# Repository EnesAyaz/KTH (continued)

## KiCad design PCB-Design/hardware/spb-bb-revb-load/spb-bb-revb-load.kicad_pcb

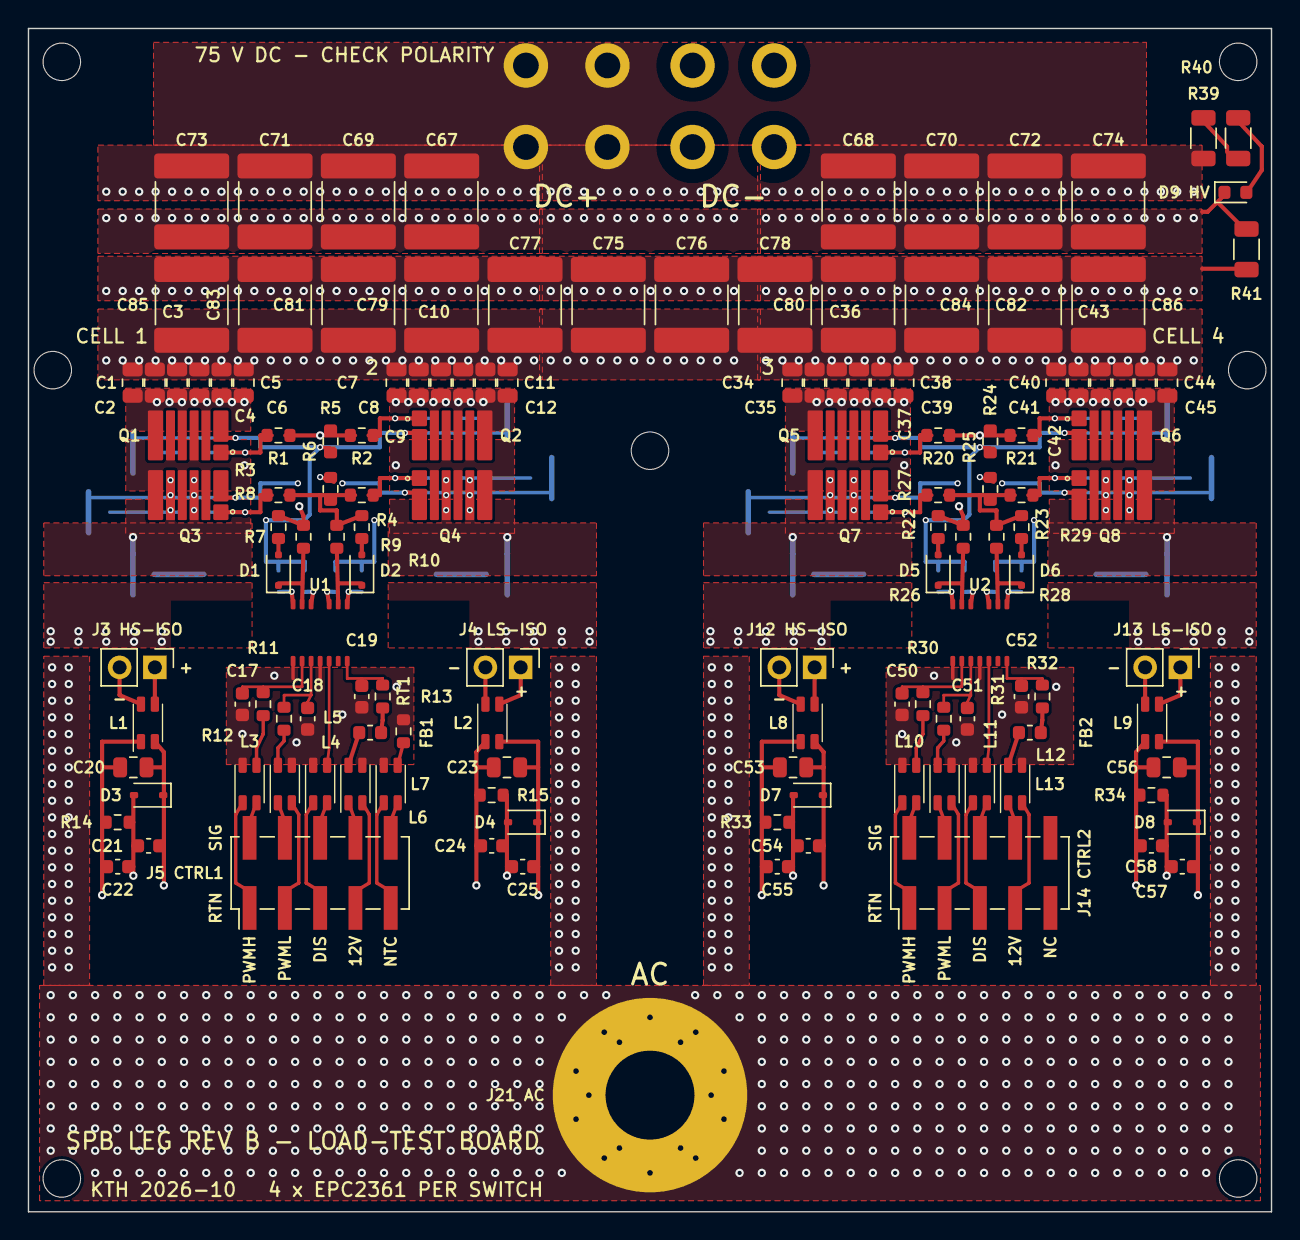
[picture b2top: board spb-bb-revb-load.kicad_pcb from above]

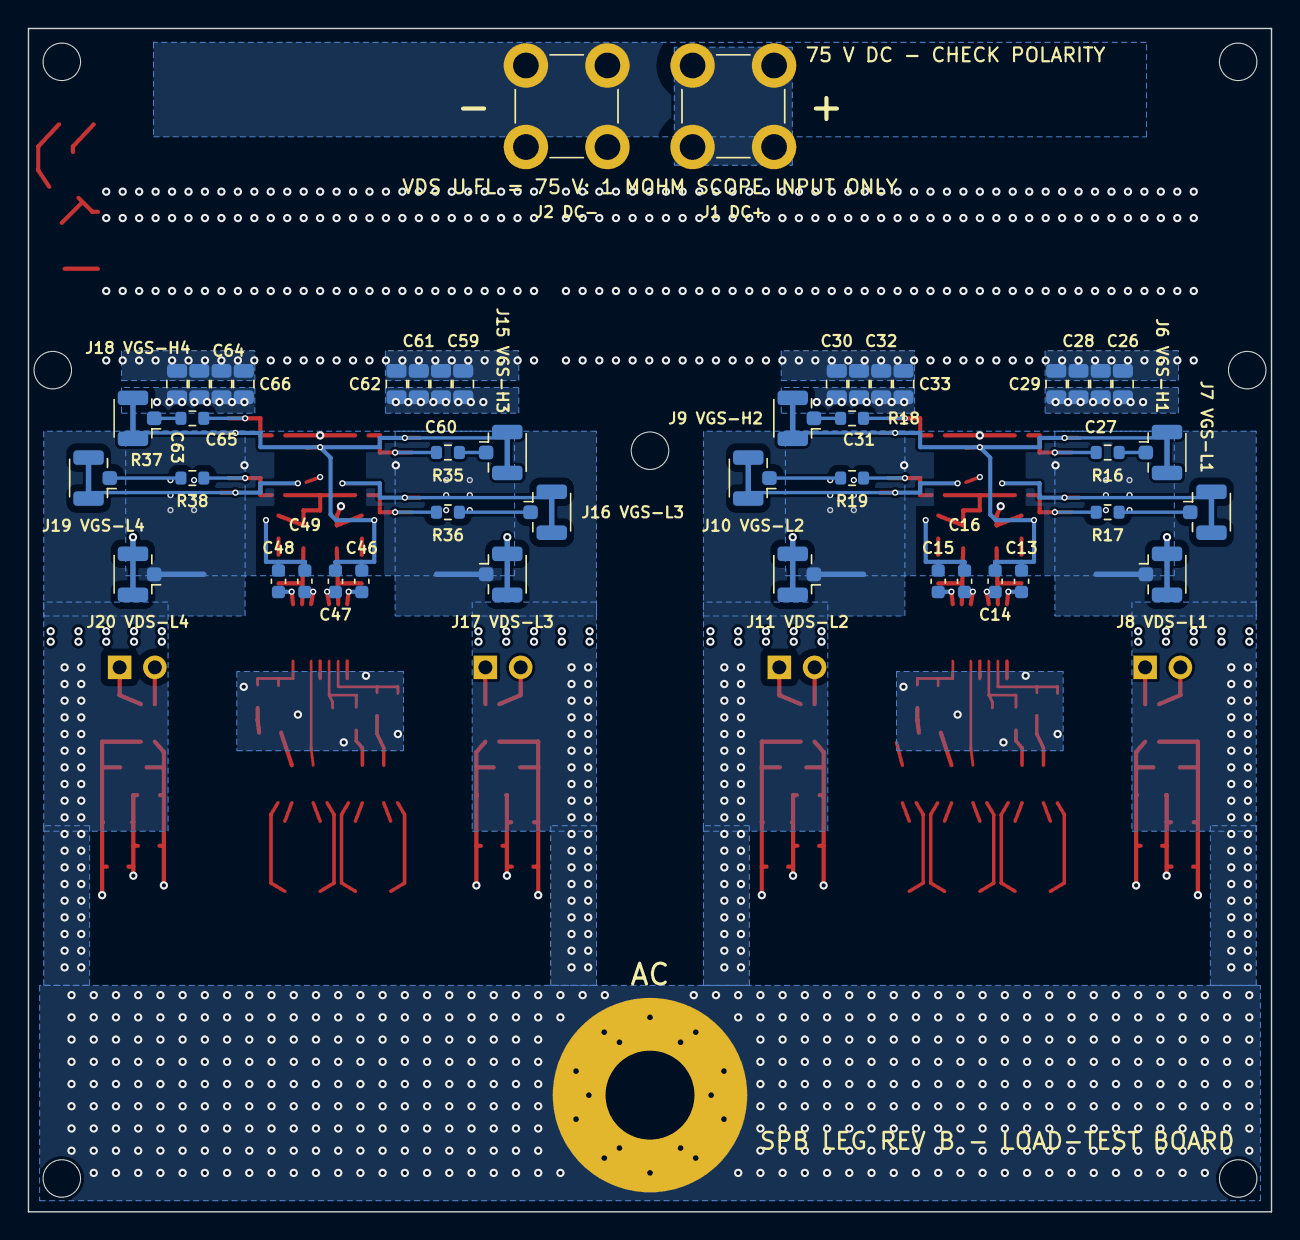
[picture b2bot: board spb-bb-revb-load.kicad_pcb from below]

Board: 4 copper layers, 89.5 x 85.2 mm, 191 parts (46 on the bottom side), 90 nets.

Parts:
C1, C2, C3, C4, C5, C6, C7, C8, C9, C10, C11, C12, C26, C27, C28, C29, C30, C31, C32, C33, C34, C35, C36, C37, C38, C39, C40, C41, C42, C43, C44, C45, C59, C60, C61, C62, C63, C64, C65, C66: 1uF 100V X7S; C_0805_2012Metric_TightCrtYd
C13, C14, C15, C16, C46, C47, C48, C49: 1uF 25V X7R 0603; C_0603_1608Metric
C17, C18, C50, C51: 100pF C0G 0603; C_0603_1608Metric
C19, C52: 22nF 25V X7R 0603; C_0603_1608Metric
C20, C23, C53, C56: 4.7uF 25V X7R 0805; C_0805_2012Metric
C21, C22, C24, C25, C54, C55, C57, C58: 4.7uF 16V X5R 0603; C_0603_1608Metric
C67, C68, C69, C70, C71, C72, C73, C74, C75, C76, C77, C78, C79, C80, C81, C82, C83, C84, C85, C86: 22uF 100V X7S 2220; C_2220_5750Metric_TightCrtYd
D1, D2, D5, D6: PMEG3020EJ; D_SOD-323F
D3, D4, D7, D8: BZX384-C5V1; D_SOD-323
D9: red 0603 (DC link present); LED_0603_1608Metric
FB1, FB2: BLM18PG221SN1 (220 R @ 100 MHz); L_0603_1608Metric
H1, H2, H3, H4: M2.5 insulated; MountingHole_2.7mm_M2.5
H5, H6, H7: M2.5 heatsink spreader; MountingHole_2.7mm_M2.5
HS1: Fischer LAM 4 K 50 12 + spreader; HS_LAM4K5012_revb
J1: DC+; Wuerth_REDCUBE-THR_WP-THRBU_74650174_THR
J2: DC-; Wuerth_REDCUBE-THR_WP-THRBU_74650174_THR
J3, J12: V_ISO,HS in: 1 +, 2 -; PinHeader_1x02_P2.54mm_Vertical
J4, J13: V_ISO,LS in: 1 +, 2 -; PinHeader_1x02_P2.54mm_Vertical
J5: CTRL1: 1 RTN 2 PWMH 3 RTN 4 PWML 5 RTN 6 DIS 7 RT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; PinHeader_2x05_P2.54mm_Vertical_SMD
J6: U.FL H1; U.FL_Hirose_U.FL-R-SMT-1_Vertical
J7: U.FL L1; U.FL_Hirose_U.FL-R-SMT-1_Vertical
J8: U.FL D1; U.FL_Hirose_U.FL-R-SMT-1_Vertical
J9: U.FL H2; U.FL_Hirose_U.FL-R-SMT-1_Vertical
J10: U.FL L2; U.FL_Hirose_U.FL-R-SMT-1_Vertical
J11: U.FL D2; U.FL_Hirose_U.FL-R-SMT-1_Vertical
J14: CTRL2: 1 RTN 2 PWMH 3 RTN 4 PWML 5 RTN 6 DIS 7 RT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; PinHeader_2x05_P2.54mm_Vertical_SMD
J15: U.FL H3; U.FL_Hirose_U.FL-R-SMT-1_Vertical
J16: U.FL L3; U.FL_Hirose_U.FL-R-SMT-1_Vertical
J17: U.FL D3; U.FL_Hirose_U.FL-R-SMT-1_Vertical
J18: U.FL H4; U.FL_Hirose_U.FL-R-SMT-1_Vertical
J19: U.FL L4; U.FL_Hirose_U.FL-R-SMT-1_Vertical
J20: U.FL D4; U.FL_Hirose_U.FL-R-SMT-1_Vertical
J21: AC; AC_BOLT_M6
L1, L2, L3, L4, L5, L6, L7, L8, L9, L10, L11, L12, L13: WE-CNSW 744232601; L_CommonMode_Wurth_WE-CNSW-1206
Q1, Q2, Q3, Q4, Q5, Q6, Q7, Q8: EPC2361
R1, R20: 0R5 1% (R_G HL); R_0603_1608Metric
R2, R21: 0R5 1% (R_G HR); R_0603_1608Metric
R3, R22: 0R5 1% (R_G LL); R_0603_1608Metric
R4, R23: 0R5 1% (R_G LR); R_0603_1608Metric
R5, R24: 10k 1% (HS gate pull-down); R_0603_1608Metric
R6, R25: 10k 1% (LS gate pull-down); R_0603_1608Metric
R7, R26: 0R75 1% (R_ON,A); R_0603_1608Metric
R8, R27: 0R (R_OFF,A); R_0603_1608Metric
R9, R28: 0R75 1% (R_ON,B); R_0603_1608Metric
R10, R29: 0R (R_OFF,B); R_0603_1608Metric
R11, R30: 47R 1% (INA); R_0603_1608Metric
R12, R31: 47R 1% (INB); R_0603_1608Metric
R13, R32: 3k 1% (RVDDI); R_0603_1608Metric
R14, R15, R33, R34: 150R 1% 0603 (bias, <= 82 mW); R_0603_1608Metric
R16, R18, R35, R37: 0R (V_GS HS); R_0603_1608Metric
R17, R19, R36, R38: 0R (V_GS LS); R_0603_1608Metric
R39, R40: 68k 1206 (HV LED); R_1206_3216Metric
R41: 100k 1206 (bleeder); R_1206_3216Metric
RT1: NTC 10k B3380 0603; R_0603_1608Metric
U1, U2: 2EDF7275K; 2EDF7275K_PG-TFLGA-13-4

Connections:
12V_CM1: FB1.1, L6.2
12V_CM2: FB2.1, L13.2
+12V1: FB1.2, R13.1
+12V2: FB2.2, R32.1
C_12V1: J5.8, L6.1
C_12V2: J14.8, L13.1
C_DIS1: J5.6, L5.4
C_DIS2: J14.6, L12.4
C_NTC1: J5.10, L7.4
C_PWMH1: J5.2, L3.4
C_PWMH2: J14.2, L10.4
C_PWML1: J5.4, L4.1
C_PWML2: J14.4, L11.1
C_RTN_12V1: J5.7, L6.4
C_RTN_12V2: J14.7, L13.4
C_RTN_DIS1: J5.5, L5.1
C_RTN_DIS2: J14.5, L12.1
C_RTN_NTC1: J5.9, L7.1
C_RTN_PWMH1: J5.1, L3.1
C_RTN_PWMH2: J14.1, L10.1
C_RTN_PWML1: J5.3, L4.4
C_RTN_PWML2: J14.3, L11.4
DCN: C1.2, C2.2, C3.2, C4.2, C5.2, C6.2, C7.2, C8.2, C9.2, C10.2, C11.2, C12.2, C26.1, C27.1, C28.1, C29.1, C30.1, C31.1, C32.1, C33.1, C34.2, C35.2, C36.2, C37.2, C38.2, C39.2, C40.2, C41.2, C42.2, C43.2, C44.2, C45.2, C59.1, C60.1, C61.1, C62.1, C63.1, C64.1, C65.1, C66.1, C67.1, C68.1, C69.1, C70.1, C71.1, C72.1, C73.1, C74.1, C75.1, C76.1, C77.1, C78.1, C79.1, C80.1, C81.1, C82.1, C83.1, C84.1, C85.1, C86.1, D9.1, J2.1, J8.2, J11.2, J17.2, J20.2, Q3.4, Q3.6, Q4.4, Q4.6, Q7.4, Q7.6, Q8.4, Q8.6, R41.2
DCP: C1.1, C2.1, C3.1, C4.1, C5.1, C6.1, C7.1, C8.1, C9.1, C10.1, C11.1, C12.1, C26.2, C27.2, C28.2, C29.2, C30.2, C31.2, C32.2, C33.2, C34.1, C35.1, C36.1, C37.1, C38.1, C39.1, C40.1, C41.1, C42.1, C43.1, C44.1, C45.1, C59.2, C60.2, C61.2, C62.2, C63.2, C64.2, C65.2, C66.2, C67.2, C68.2, C69.2, C70.2, C71.2, C72.2, C73.2, C74.2, C75.2, C76.2, C77.2, C78.2, C79.2, C80.2, C81.2, C82.2, C83.2, C84.2, C85.2, C86.2, J1.1, Q1.3, Q1.5, Q1.7, Q2.3, Q2.5, Q2.7, Q5.3, Q5.5, Q5.7, Q6.3, Q6.5, Q6.7, R39.1, R41.1
DIS1: L5.3, U1.5
DIS2: L12.3, U2.5
GH_L1: Q1.1, R1.1, R16.2
GH_L2: Q5.1, R20.1, R35.2
GH_R1: Q2.1, R2.2, R18.1
GH_R2: Q6.1, R21.2, R37.1
GH_STAR1: R1.2, R2.1, R5.2, R7.2, R8.2
GH_STAR2: R20.2, R21.1, R24.2, R26.2, R27.2
GL_L1: Q3.1, R3.1, R17.2
GL_L2: Q7.1, R22.1, R36.2
GL_R1: Q4.1, R4.2, R19.1
GL_R2: Q8.1, R23.2, R38.1
GL_STAR1: R3.2, R4.1, R6.1, R9.2, R10.2
GL_STAR2: R22.2, R23.1, R25.1, R28.2, R29.2
GNDI1: C17.1, C18.1, C19.1, L3.2, L4.3, L5.2, L6.3, L7.2, RT1.2, U1.1, U1.4
GNDI2: C50.1, C51.1, C52.1, L10.2, L11.3, L12.2, L13.3, U2.1, U2.4
HVA: R39.2, R40.1
HVB: D9.2, R40.2
INA1: C17.2, R11.2, U1.2
INA2: C50.2, R30.2, U2.2
INB1: C18.2, R12.2, U1.3
INB2: C51.2, R31.2, U2.3
KH1: C13.1, C14.1, C21.1, C22.2, D3.2, J6.2, J9.2, Q1.2, Q2.2, R5.1, R14.2
KH2: C46.1, C47.1, C54.1, C55.2, D7.2, J15.2, J18.2, Q5.2, Q6.2, R24.1, R33.2
KL1: C15.1, C16.1, C24.2, C25.1, D4.2, J7.2, J10.2, Q3.2, Q4.2, R6.2, R15.2
KL2: C48.1, C49.1, C57.2, C58.1, D8.2, J16.2, J19.2, Q7.2, Q8.2, R25.2, R34.2
NTC: L7.3, RT1.1
OFFA1: D1.2, R8.1
OFFA2: D5.2, R27.1
OFFB1: D2.2, R10.1
OFFB2: D6.2, R29.1
OUTA1: D1.1, R7.1, U1.12
OUTA2: D5.1, R26.1, U2.12
OUTB1: D2.1, R9.1, U1.9
OUTB2: D6.1, R28.1, U2.9
PWM_H1: L3.3, R11.1
PWM_H2: L10.3, R30.1
PWM_L1: L4.2, R12.1
PWM_L2: L11.2, R31.1
SW: J8.1, J11.1, J17.1, J20.1, J21.1, Q1.4, Q1.6, Q2.4, Q2.6, Q3.3, Q3.5, Q3.7, Q4.3, Q4.5, Q4.7, Q5.4, Q5.6, Q6.4, Q6.6, Q7.3, Q7.5, Q7.7, Q8.3, Q8.5, Q8.7
UFL_H1: J6.1, R16.1
UFL_H2: J9.1, R18.2
UFL_H3: J15.1, R35.1
UFL_H4: J18.1, R37.2
UFL_L1: J7.1, R17.1
UFL_L2: J10.1, R19.2
UFL_L3: J16.1, R36.1
UFL_L4: J19.1, R38.2
VDDA1: C13.2, C20.2, C21.2, D3.1, L1.4, U1.13
VDDA2: C46.2, C53.2, C54.2, D7.1, L8.4, U2.13
VDDB1: C16.2, C23.2, C25.2, D4.1, L2.4, U1.10
VDDB2: C49.2, C56.2, C58.2, D8.1, L9.4, U2.10
VDDI1: C19.2, R13.2, U1.7
VDDI2: C52.2, R32.2, U2.7
VEEA1: C14.2, C20.1, C22.1, L1.1, R14.1, U1.11
VEEA2: C47.2, C53.1, C55.1, L8.1, R33.1, U2.11
VEEB1: C15.2, C23.1, C24.1, L2.1, R15.1, U1.8
VEEB2: C48.2, C56.1, C57.1, L9.1, R34.1, U2.8
VINA_N1: J3.2, L1.2
VINA_N2: J12.2, L8.2
VINA_P1: J3.1, L1.3
VINA_P2: J12.1, L8.3
VINB_N1: J4.2, L2.2
VINB_N2: J13.2, L9.2
VINB_P1: J4.1, L2.3
VINB_P2: J13.1, L9.3

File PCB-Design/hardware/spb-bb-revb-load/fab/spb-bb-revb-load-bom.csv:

"# 4 layers, 1.6 mm FR4, 2 oz (70 um) on all layers, L1-L2 and L3-L4 prepreg 0.1 mm, ENIG; BLIND vias L1-L2 (0.25 mm drill) filled + capped in the LS source pads; load-test board; IPC class 2; solder mask over all copper and ALL vias tented (the 1200 V control/power barrier relies on it)"
Qty,References,Value,Footprint,Manufacturer part / note,Fit
2,J1 J2,DC+,Wuerth_REDCUBE-THR_WP-THRBU_74650174_THR,"Wuerth 74650174 (REDCUBE THR, M4)",fit
8,Q1 Q2 Q3 Q4 Q5 Q6 Q7 Q8,EPC2361,EPC2361,EPC2361,fit
40,C1 C10 C11 C12 C2 C26 C27 C28 C29 C3 C30 C31 C32 C33 C34 C35 C36 C37 C38 C39 C4 C40 C41 C42 C43 C44 C45 C5 C59 C6 C60 C61 C62 C63 C64 C65 C66 C7 C8 C9,1uF 100V X7S,C_0805_2012Metric_TightCrtYd,TDK C2012X7S2A105K125AB,fit
8,R1 R2 R20 R21 R22 R23 R3 R4,0R5 1% (R_G HL),R_0603_1608Metric,0.5R 0603 1% (Panasonic ERJ-3BQFR50V),fit
4,R24 R25 R5 R6,10k 1% (HS gate pull-down),R_0603_1608Metric,10k 0603 1%,fit
2,U1 U2,2EDF7275K,2EDF7275K_PG-TFLGA-13-4,Infineon 2EDF7275KXUMA1,fit
4,R26 R28 R7 R9,"0R75 1% (R_ON,A)",R_0603_1608Metric,0.75R 0603 1% (Panasonic ERJ-3RQFR75V),fit
4,R10 R27 R29 R8,"0R (R_OFF,A)",R_0603_1608Metric,0R 0603 jumper (set R_OFF here),fit
4,D1 D2 D5 D6,PMEG3020EJ,D_SOD-323F,"Nexperia PMEG3020EJ (30 V, 2 A, SOD323F)",fit
8,C13 C14 C15 C16 C46 C47 C48 C49,1uF 25V X7R 0603,C_0603_1608Metric,TDK C1608X7R1E105K080AB,fit
4,C17 C18 C50 C51,100pF C0G 0603,C_0603_1608Metric,Murata GRM1885C1H101JA01,fit
4,R11 R12 R30 R31,47R 1% (INA),R_0603_1608Metric,47R 0603 1%,fit
2,C19 C52,22nF 25V X7R 0603,C_0603_1608Metric,Murata GRM188R71E223KA01,fit
2,R13 R32,3k 1% (RVDDI),R_0603_1608Metric,3.0k 0603 1%,fit
4,J12 J13 J3 J4,"V_ISO,HS in: 1 +, 2 -",PinHeader_1x02_P2.54mm_Vertical,2.54 mm header 1x2,fit
13,L1 L10 L11 L12 L13 L2 L3 L4 L5 L6 L7 L8 L9,WE-CNSW 744232601,L_CommonMode_Wurth_WE-CNSW-1206,"Wurth 744232601 (600 Ohm @ 100 MHz, 260 mA)",fit
4,C20 C23 C53 C56,4.7uF 25V X7R 0805,C_0805_2012Metric,Murata GRM21BR71E475KA73,fit
4,D3 D4 D7 D8,BZX384-C5V1,D_SOD-323,"Nexperia BZX384-C5V1 (5.1 V, 300 mW)",fit
4,R14 R15 R33 R34,"150R 1% 0603 (bias, <= 82 mW)",R_0603_1608Metric,150R 0603 1% 0.1 W,fit
8,C21 C22 C24 C25 C54 C55 C57 C58,4.7uF 16V X5R 0603,C_0603_1608Metric,Murata GRM188R61C475KAAJ,fit
2,J14 J5,CTRL1: 1 RTN 2 PWMH 3 RTN 4 PWML 5 RTN 6 DIS 7 RTN 8 12V 9 RTN 10 NTC,PinHeader_2x05_P2.54mm_Vertical_SMD,"Samtec TSM-105-01-T-DV (2 x 5, 2.54 mm, SMT)",fit
2,FB1 FB2,BLM18PG221SN1 (220 R @ 100 MHz),L_0603_1608Metric,"Murata BLM18PG221SN1D (ferrite bead, 1.4 A)",fit
1,RT1,NTC 10k B3380 0603,R_0603_1608Metric,Murata NCP18XH103F03RB,fit
8,J10 J15 J16 J18 J19 J6 J7 J9,U.FL H1,U.FL_Hirose_U.FL-R-SMT-1_Vertical,Hirose U.FL-R-SMT-1(10),fit
8,R16 R17 R18 R19 R35 R36 R37 R38,0R (V_GS HS),R_0603_1608Metric,0R 0603,fit
4,J11 J17 J20 J8,U.FL D1,U.FL_Hirose_U.FL-R-SMT-1_Vertical,"Hirose U.FL-R-SMT-1(01) - 100 V listed, confirm",fit
20,C67 C68 C69 C70 C71 C72 C73 C74 C75 C76 C77 C78 C79 C80 C81 C82 C83 C84 C85 C86,22uF 100V X7S 2220,C_2220_5750Metric_TightCrtYd,TDK C5750X7S2A226M280KB,fit
2,R39 R40,68k 1206 (HV LED),R_1206_3216Metric,68k 1206 1% 200 V,fit
1,D9,red 0603 (DC link present),LED_0603_1608Metric,Wurth 150060RS75000,fit
1,R41,100k 1206 (bleeder),R_1206_3216Metric,100k 1206 1% 200 V,fit

Mechanical (not placed by the assembler)
1,HS1,"Fan heatsink 40 x 40 x 50 mm, 12 V fan",-,"Fischer Elektronik LAM 4 K 50 12 (0.65 K/W), Farnell 4708974"
1,HS1,Fan supply: 12 V from the bench supply (no fan header on the board: 1200 V barrier),-,-
2,"J5, J14",Control cable: 2 x 5 IDC socket + ribbon (each signal next to its own return),-,"2.54 mm IDC, e.g. Wurth 61201021621"
1,HS1,"Heat spreader Al 6061, 89.5 x 12.8 x 3 mm, 4 pedestals 5.6 x 7.7 x 0.6 mm over the cells, 3 x M2.5 (H5-H7)",-,machined
4,HS1,"Insulating gap pad over each cell, 5.6 x 7.7 mm, 0.5 mm, >= 5 W/mK",-,"Bergquist TGP 5000 0.020 in, cut to size, or equivalent"
3,H5-H7,M2.5 x 10 screw + insulating shoulder washer (spreader),-,nylon or steel + washer
4,H1-H4,M2.5 standoff + screw (H3/H4: nylon M2.5 x 6.5 mm onto the busbar),-,nylon
2,J1-J2,M4 x 8 screw + washer from below through the busbar into the REDCUBE,-,"steel, A2"
1,J22,"M6 x 16 bolt + nut + 2 washers, AC bolt pad",-,"steel, A2"
1,J22,AC bar 12 x 5 mm Cu through a LEM HO 250-S,-,Cu-ETP + LEM HO 250-S

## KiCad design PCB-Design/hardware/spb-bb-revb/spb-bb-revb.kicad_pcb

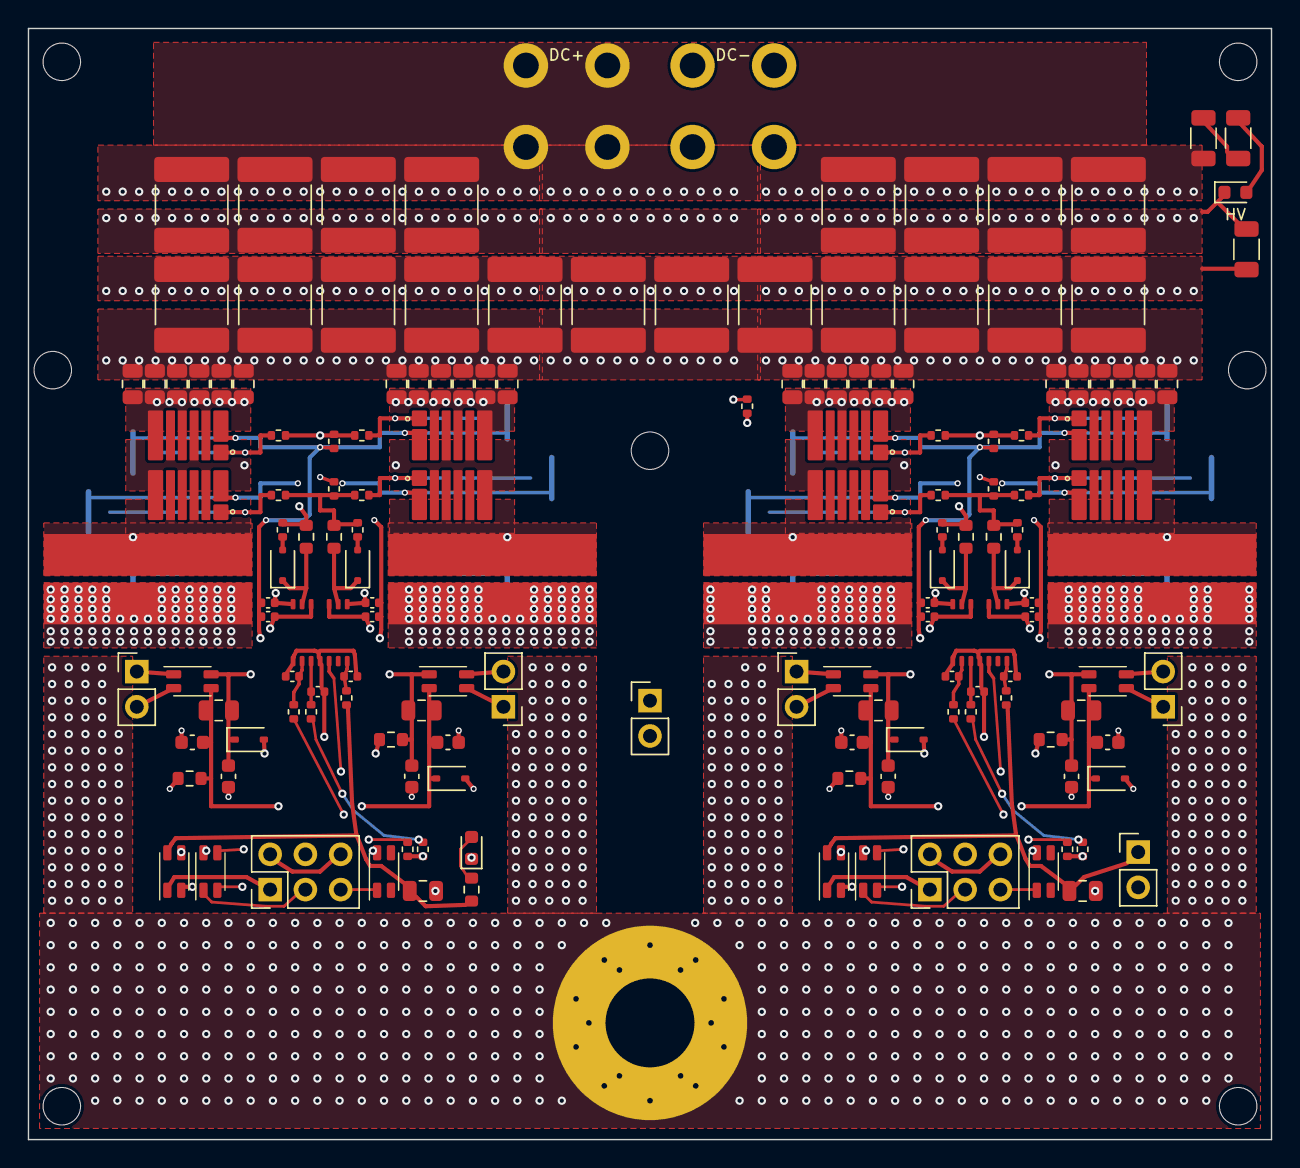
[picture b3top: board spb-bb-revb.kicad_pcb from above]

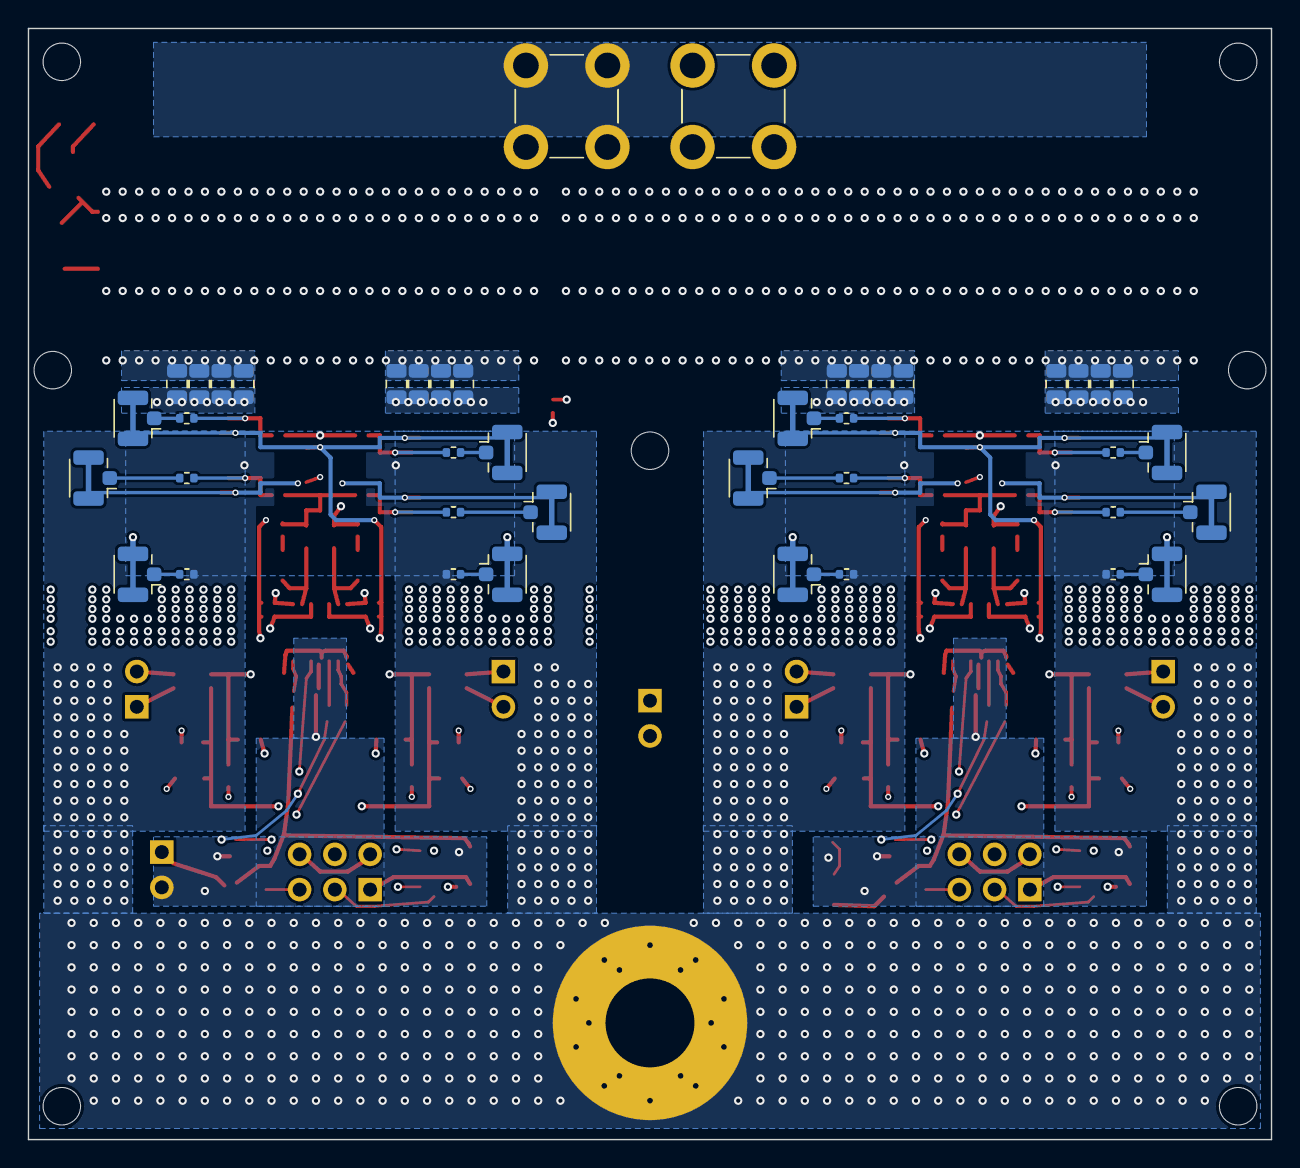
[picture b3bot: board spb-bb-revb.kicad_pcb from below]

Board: 4 copper layers, 89.5 x 80.0 mm, 204 parts (42 on the bottom side), 89 nets.

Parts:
C1, C2, C3, C4, C5, C6, C7, C8, C9, C10, C11, C12, C27, C28, C29, C30, C31, C32, C33, C34, C35, C36, C37, C38, C39, C40, C41, C42, C43, C44, C45, C46, C61, C62, C63, C64, C65, C66, C67, C68: 1uF 100V X7S; C_0805_2012Metric_TightCrtYd
C13, C14, C15, C16, C47, C48, C49, C50: 1uF 16V X7R 0402; C_0402_1005Metric
C17, C18, C51, C52: 100pF C0G 0402; C_0402_1005Metric
C19, C53: 22nF 25V X7R 0402; C_0402_1005Metric
C20, C23, C54, C57: 4.7uF 25V X7R 0805; C_0805_2012Metric
C21, C22, C24, C25, C55, C56, C58, C59: 4.7uF 16V X5R 0603; C_0603_1608Metric
C26, C60: 4.7uF 25V X7R 0805 (12 V); C_0805_2012Metric
C69, C70, C71, C72, C73, C74, C75, C76, C77, C78, C79, C80, C81, C82, C83, C84, C85, C86, C87, C88: 22uF 100V X7S 2220; C_2220_5750Metric_TightCrtYd
D1, D2, D6, D7: PMEG3020EJ; D_SOD-323F
D3, D4, D8, D9: BZX384-C5V1; D_SOD-323
D5: green 0603 (12 V); LED_0603_1608Metric
D10: red 0603 (DC link present); LED_0603_1608Metric
H1, H2, H3, H4: M2.5 insulated; MountingHole_2.7mm_M2.5
H5, H6, H7: M2.5 heatsink spreader; MountingHole_2.7mm_M2.5
HS1: Fischer LAM 4 (100 mm) + spreader; HS_LAM4K10012_revb
J1: DC+; Wuerth_REDCUBE-THR_WP-THRBU_74650174_THR
J2: DC-; Wuerth_REDCUBE-THR_WP-THRBU_74650174_THR
J3, J12: V_ISO,HS in: 1 +, 2 -; PinHeader_1x02_P2.54mm_Vertical
J4, J13: V_ISO,LS in: 1 +, 2 -; PinHeader_1x02_P2.54mm_Vertical
J5: CTRL1: 1 12V 2 GND 3 PWM_H 4 PWM_L 5 DIS 6 GND; PinHeader_2x03_P2.54mm_Vertical
J6: U.FL H1; U.FL_Hirose_U.FL-R-SMT-1_Vertical
J7: U.FL L1; U.FL_Hirose_U.FL-R-SMT-1_Vertical
J8: U.FL D1; U.FL_Hirose_U.FL-R-SMT-1_Vertical
J9: U.FL H2; U.FL_Hirose_U.FL-R-SMT-1_Vertical
J10: U.FL L2; U.FL_Hirose_U.FL-R-SMT-1_Vertical
J11: U.FL D2; U.FL_Hirose_U.FL-R-SMT-1_Vertical
J14: CTRL2: 1 12V 2 GND 3 PWM_H 4 PWM_L 5 DIS 6 GND; PinHeader_2x03_P2.54mm_Vertical
J15: FAN 12V: 1 +12V, 2 GND; PinHeader_1x02_P2.54mm_Vertical
J16: U.FL H3; U.FL_Hirose_U.FL-R-SMT-1_Vertical
J17: U.FL L3; U.FL_Hirose_U.FL-R-SMT-1_Vertical
J18: U.FL D3; U.FL_Hirose_U.FL-R-SMT-1_Vertical
J19: U.FL H4; U.FL_Hirose_U.FL-R-SMT-1_Vertical
J20: U.FL L4; U.FL_Hirose_U.FL-R-SMT-1_Vertical
J21: U.FL D4; U.FL_Hirose_U.FL-R-SMT-1_Vertical
J22: AC; AC_BOLT_M6
J23: 1:NTC 2:DC- (LS domain!); PinHeader_1x02_P2.54mm_Vertical
L1, L2, L3, L4, L5, L6, L7, L8, L9, L10: WE-CNSW 744232601; L_CommonMode_Wurth_WE-CNSW-1206
Q1, Q2, Q3, Q4, Q5, Q6, Q7, Q8: EPC2361
R1, R25: 0R5 1% (R_G HL); R_0402_1005Metric
R2, R26: 0R5 1% (R_G HR); R_0402_1005Metric
R3, R27: 0R5 1% (R_G LL); R_0402_1005Metric
R4, R28: 0R5 1% (R_G LR); R_0402_1005Metric
R5, R29: 10k 1% (HS gate pull-down); R_0402_1005Metric
R6, R30: 10k 1% (LS gate pull-down); R_0402_1005Metric
R7, R31: 0R75 1% (R_ON,A); R_0603_1608Metric
R8, R32: 0R (R_OFF,A); R_0402_1005Metric
R9, R33: 0R75 1% (R_ON,B); R_0603_1608Metric
R10, R34: 0R (R_OFF,B); R_0402_1005Metric
R11, R35: 47R 1% (INA); R_0402_1005Metric
R12, R36: 47R 1% (INB); R_0402_1005Metric
R13, R37: 3k 1% (RVDDI); R_0402_1005Metric
R14, R15, R38, R39: 150R 1% 0603 (bias, <= 82 mW); R_0603_1608Metric
R16, R40: 10k (PWM_H pull-down); R_0402_1005Metric
R17, R41: 10k (PWM_L pull-down); R_0402_1005Metric
R18: 4.7k (LED); R_0603_1608Metric
R19, R22, R42, R45: 0R (V_GS HS); R_0402_1005Metric
R20, R23, R43, R46: 0R (V_GS LS); R_0402_1005Metric
R21, R24, R44, R47: 953R 1% (V_DS LS, 20:1 into 50 R); R_0402_1005Metric
R48, R49: 68k 1206 (HV LED); R_1206_3216Metric
R50: 100k 1206 (bleeder); R_1206_3216Metric
RS1, RS2, RS3, RS4: UFCS-R001; PMK_UFCS_R001
RT1: NTC 10k B3380; R_0402_1005Metric
U1, U2: 2EDF7275K; 2EDF7275K_PG-TFLGA-13-4

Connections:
+12V1: C26.1, L3.2, R13.1, R18.1
+12V2: C60.1, J15.1, L8.2, R37.1
C_12V1: J5.1, L3.1
C_12V2: J14.1, L8.1
C_DIS1: J5.5, L5.1
C_DIS2: J14.5, L10.1
C_GND1: J5.2, J5.6, L3.4
C_GND2: J14.2, J14.6, L8.4
C_PWMH1: J5.3, L4.1
C_PWMH2: J14.3, L9.1
C_PWML1: J5.4, L4.4
C_PWML2: J14.4, L9.4
DCN: C1.2, C2.2, C3.2, C4.2, C5.2, C6.2, C7.2, C8.2, C9.2, C10.2, C11.2, C12.2, C27.1, C28.1, C29.1, C30.1, C31.1, C32.1, C33.1, C34.1, C35.2, C36.2, C37.2, C38.2, C39.2, C40.2, C41.2, C42.2, C43.2, C44.2, C45.2, C46.2, C61.1, C62.1, C63.1, C64.1, C65.1, C66.1, C67.1, C68.1, C69.1, C70.1, C71.1, C72.1, C73.1, C74.1, C75.1, C76.1, C77.1, C78.1, C79.1, C80.1, C81.1, C82.1, C83.1, C84.1, C85.1, C86.1, C87.1, C88.1, D10.1, J2.1, J23.2, R50.2, RS1.2, RS2.2, RS3.2, RS4.2, RT1.1
DCP: C1.1, C2.1, C3.1, C4.1, C5.1, C6.1, C7.1, C8.1, C9.1, C10.1, C11.1, C12.1, C27.2, C28.2, C29.2, C30.2, C31.2, C32.2, C33.2, C34.2, C35.1, C36.1, C37.1, C38.1, C39.1, C40.1, C41.1, C42.1, C43.1, C44.1, C45.1, C46.1, C61.2, C62.2, C63.2, C64.2, C65.2, C66.2, C67.2, C68.2, C69.2, C70.2, C71.2, C72.2, C73.2, C74.2, C75.2, C76.2, C77.2, C78.2, C79.2, C80.2, C81.2, C82.2, C83.2, C84.2, C85.2, C86.2, C87.2, C88.2, J1.1, Q1.3, Q1.5, Q1.7, Q2.3, Q2.5, Q2.7, Q5.3, Q5.5, Q5.7, Q6.3, Q6.5, Q6.7, R48.1, R50.1
DIS1: L5.2, U1.5
DIS2: L10.2, U2.5
GH_L1: Q1.1, R1.1, R19.2
GH_L2: Q5.1, R25.1, R42.2
GH_R1: Q2.1, R2.2, R22.1
GH_R2: Q6.1, R26.2, R45.1
GH_STAR1: R1.2, R2.1, R5.2, R7.2, R8.2
GH_STAR2: R25.2, R26.1, R29.2, R31.2, R32.2
GL_L1: Q3.1, R3.1, R20.2
GL_L2: Q7.1, R27.1, R43.2
GL_R1: Q4.1, R4.2, R23.1
GL_R2: Q8.1, R28.2, R46.1
GL_STAR1: R3.2, R4.1, R6.1, R9.2, R10.2
GL_STAR2: R27.2, R28.1, R30.1, R33.2, R34.2
GNDI1: C17.1, C18.2, C19.2, C26.2, D5.1, L3.3, R16.1, R17.1, U1.1, U1.4
GNDI2: C51.1, C52.2, C53.2, C60.2, J15.2, L8.3, R40.1, R41.1, U2.1, U2.4
HVA: R48.2, R49.1
HVB: D10.2, R49.2
INA1: C17.2, R11.2, U1.2
INA2: C51.2, R35.2, U2.2
INB1: C18.1, R12.2, U1.3
INB2: C52.1, R36.2, U2.3
KH1: C13.1, C14.1, C21.1, C22.1, D3.2, J6.2, J9.2, Q1.2, Q2.2, R5.1, R14.1
KH2: C47.1, C48.1, C55.1, C56.1, D8.2, J16.2, J19.2, Q5.2, Q6.2, R29.1, R38.1
KL1: C15.2, C16.2, C24.1, C25.2, D4.2, J7.2, J10.2, Q3.2, Q4.2, R6.2, R15.1
KL2: C49.2, C50.2, C58.1, C59.2, D9.2, J17.2, J20.2, Q7.2, Q8.2, R30.2, R39.1
LEDA_12V1: D5.2, R18.2
LSRC1: J8.2, Q3.4, Q3.6, RS1.1
LSRC2: J11.2, Q4.4, Q4.6, RS2.1
LSRC3: J18.2, Q7.4, Q7.6, RS3.1
LSRC4: J21.2, Q8.4, Q8.6, RS4.1
NTC: J23.1, RT1.2
OFFA1: D1.2, R8.1
OFFA2: D6.2, R32.1
OFFB1: D2.2, R10.1
OFFB2: D7.2, R34.1
OUTA1: D1.1, R7.1, U1.12
OUTA2: D6.1, R31.1, U2.12
OUTB1: D2.1, R9.1, U1.9
OUTB2: D7.1, R33.1, U2.9
PWM_H1: L4.2, R11.1, R16.2
PWM_H2: L9.2, R35.1, R40.2
PWM_L1: L4.3, R12.1, R17.2
PWM_L2: L9.3, R36.1, R41.2
SW: J22.1, Q1.4, Q1.6, Q2.4, Q2.6, Q3.3, Q3.5, Q3.7, Q4.3, Q4.5, Q4.7, Q5.4, Q5.6, Q6.4, Q6.6, Q7.3, Q7.5, Q7.7, Q8.3, Q8.5, Q8.7, R21.2, R24.1, R44.2, R47.1
UFL_D1: J8.1, R21.1
UFL_D2: J11.1, R24.2
UFL_D3: J18.1, R44.1
UFL_D4: J21.1, R47.2
UFL_H1: J6.1, R19.1
UFL_H2: J9.1, R22.2
UFL_H3: J16.1, R42.1
UFL_H4: J19.1, R45.2
UFL_L1: J7.1, R20.1
UFL_L2: J10.1, R23.2
UFL_L3: J17.1, R43.1
UFL_L4: J20.1, R46.2
VDDA1: C13.2, C20.2, C21.2, D3.1, L1.2, U1.13
VDDA2: C47.2, C54.2, C55.2, D8.1, L6.2, U2.13
VDDB1: C16.1, C23.2, C25.1, D4.1, L2.4, U1.10
VDDB2: C50.1, C57.2, C59.1, D9.1, L7.4, U2.10
VDDI1: C19.1, R13.2, U1.7
VDDI2: C53.1, R37.2, U2.7
VEEA1: C14.2, C20.1, C22.2, L1.3, R14.2, U1.11
VEEA2: C48.2, C54.1, C56.2, L6.3, R38.2, U2.11
VEEB1: C15.1, C23.1, C24.2, L2.1, R15.2, U1.8
VEEB2: C49.1, C57.1, C58.2, L7.1, R39.2, U2.8
VINA_N1: J3.2, L1.4
VINA_N2: J12.2, L6.4
VINA_P1: J3.1, L1.1
VINA_P2: J12.1, L6.1
VINB_N1: J4.2, L2.2
VINB_N2: J13.2, L7.2
VINB_P1: J4.1, L2.3
VINB_P2: J13.1, L7.3
